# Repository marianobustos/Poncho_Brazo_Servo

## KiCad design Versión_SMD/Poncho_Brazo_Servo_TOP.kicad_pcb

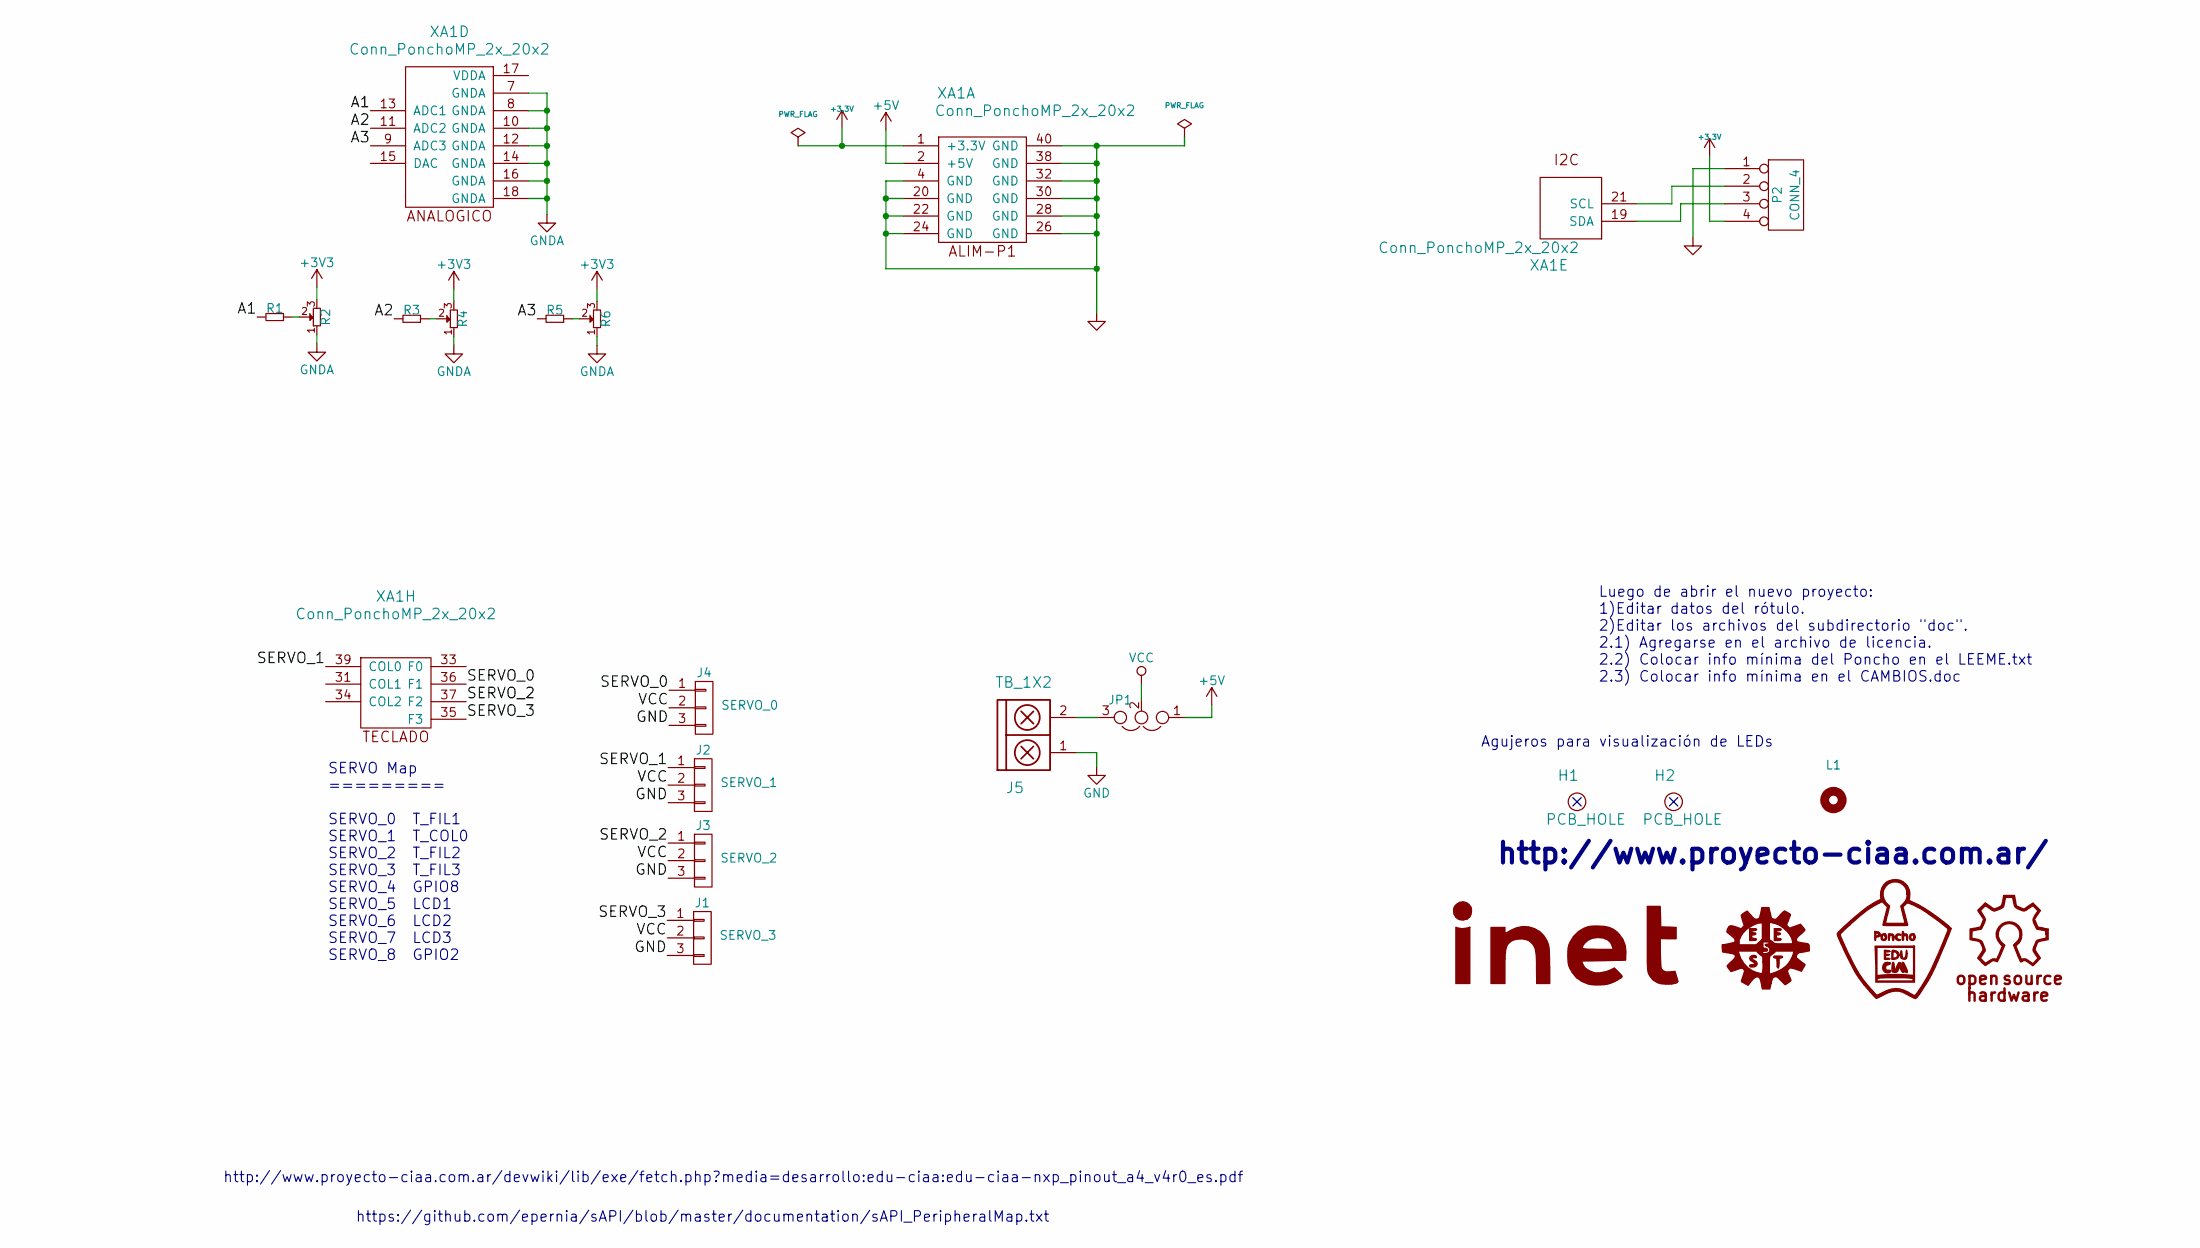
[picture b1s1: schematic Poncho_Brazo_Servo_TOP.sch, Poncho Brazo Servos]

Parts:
H1, H2: PCB_HOLE; Led_Hole
J1: SERVO_3; Pin_Strip_3
J2: SERVO_1; Pin_Strip_3
J3: SERVO_2; Pin_Strip_3
J4: SERVO_0; Pin_Strip_3
J5: TB_1X2; BORNERA2_AZUL
JP1: Jumper_NC_Dual; Pin_Strip_3
L1: Mounting_Hole; LOGO_INET_CHICO
P2: CONN_4; pin_strip_4
R1, R3, R5: R; R_1206
R2, R4, R6: POT; Potenciometro_Perilla_Aluminio
XA1: Conn_PonchoMP_2x_20x2; Conn_Poncho_Derecha

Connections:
+5V: JP1.1, XA1.2 (+5V)
/A1: R1.2, XA1.13 (ADC1)
/A2: R3.2, XA1.11 (ADC2)
/A3: R5.2, XA1.9 (ADC3)
/SERVO_0: J4.1, XA1.36 (F1)
/SERVO_1: J2.1, XA1.39 (COL0)
/SERVO_2: J3.1, XA1.37 (F2)
/SERVO_3: J1.1, XA1.35 (F3)
GND: J1.3, J2.3, J3.3, J4.3, J5.1, P2.1, XA1.4 (GND), XA1.20 (GND), XA1.22 (GND), XA1.24 (GND), XA1.26 (GND), XA1.28 (GND), XA1.30 (GND), XA1.32 (GND), XA1.38 (GND), XA1.40 (GND)
GNDA: R2.1, R4.1, R6.1, XA1.7 (GNDA), XA1.8 (GNDA), XA1.10 (GNDA), XA1.12 (GNDA), XA1.14 (GNDA), XA1.16 (GNDA), XA1.18 (GNDA)
unnamed: J5.2, JP1.3
unnamed: P2.2, XA1.21 (SCL)
unnamed: P2.3, XA1.19 (SDA)
unnamed: R1.1, R2.2
unnamed: R3.1, R4.2
unnamed: R5.1, R6.2
VCC: J1.2, J2.2, J3.2, J4.2, JP1.2

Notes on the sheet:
http://www.proyecto-ciaa.com.ar/
Luego de abrir el nuevo proyecto: 1)Editar datos del rótulo. 2)Editar los archivos del subdirectorio "doc". 2.1) Agregarse en el archivo de licencia. 2.2) Colocar info mínima del Poncho en el LEEME.txt 2.3) Colocar info mínima en el CAMBIOS.doc
Agujeros para visualización de LEDs
SERVO Map ========= SERVO_0 T_FIL1 SERVO_1 T_COL0 SERVO_2 T_FIL2 SERVO_3 T_FIL3 SERVO_4 GPIO8 SERVO_5 LCD1 SERVO_6 LCD2 SERVO_7 LCD3 SERVO_8 GPIO2
https://github.com/epernia/sAPI/blob/master/documentation/sAPI_PeripheralMap.txt
http://www.proyecto-ciaa.com.ar/devwiki/lib/exe/fetch.php?media=desarrollo:edu-ciaa:edu-ciaa-nxp_pinout_a4_v4r0_es.pdf

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
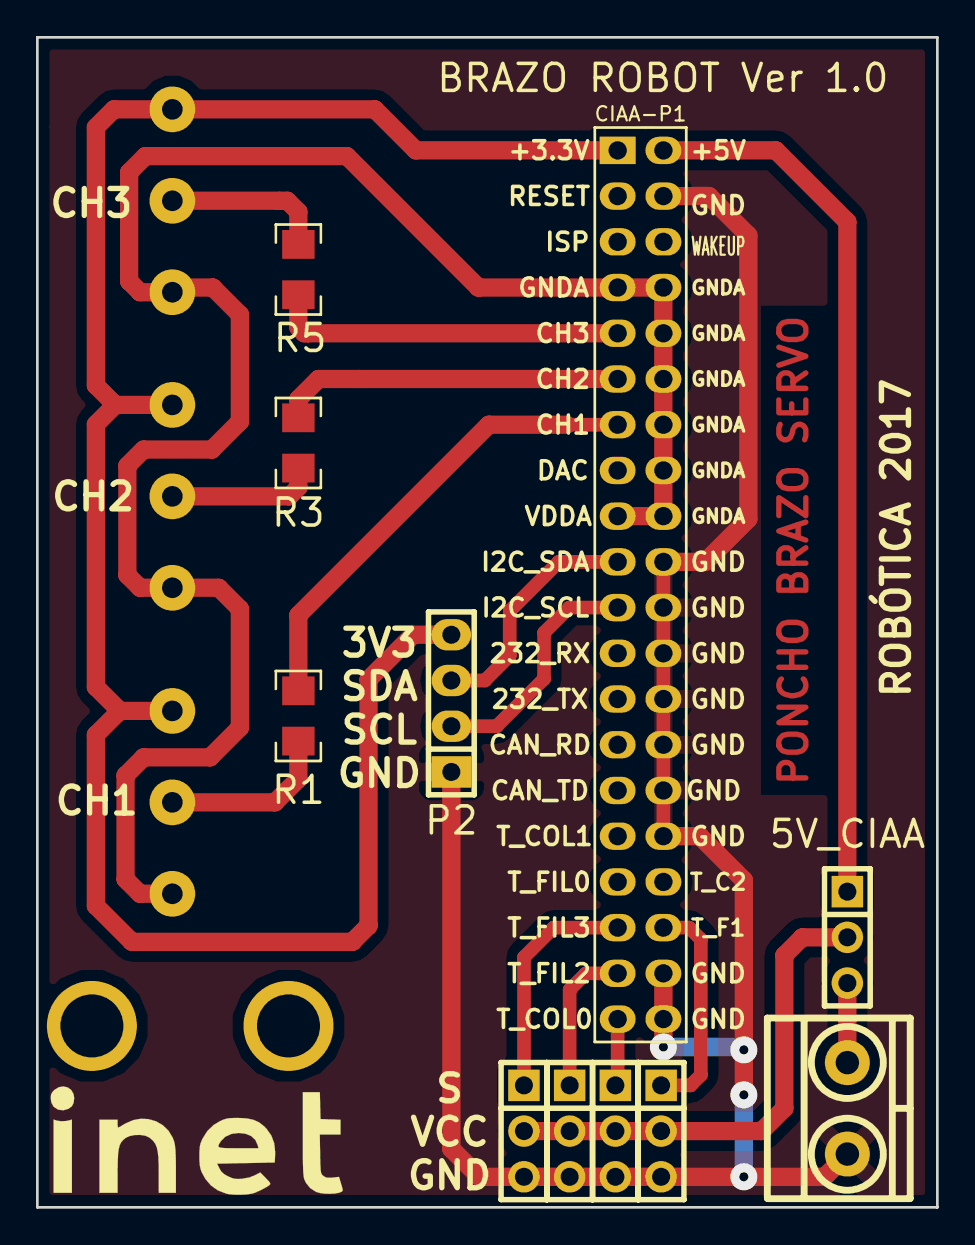
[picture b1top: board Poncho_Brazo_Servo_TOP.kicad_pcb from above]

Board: 2 copper layers, 50.0 x 65.0 mm, 17 parts (0 on the bottom side), 18 nets.

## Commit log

2017-09-28 Versión inicial
2017-09-28 Docs
    Se agregaron los archivos de documentación.
2017-09-28 Versión SMD y SCH en pdf
    Se agrega una nueva versión de pcb y se generó el SCH en formato PDF
